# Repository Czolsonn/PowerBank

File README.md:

# STM32 Solar PowerBank

Projekt inteligentnego PowerBanka sterowanego mikrokontrolerem z rodziny **STM32F1**, integrującego ładowanie fotowoltaiczne z zaawansowanym zarządzaniem energią.

## 📋 Opis Projektu

Urządzenie łączy funkcję magazynu energii (ogniwa 18650) z inteligentnym systemem sterowania. Wykorzystuje synchroniczną przetwornicę Buck do efektywnego obniżania napięcia oraz dedykowane kontrolery USB do bezpiecznego ładowania urządzeń zewnętrznych.

### Kluczowe parametry techniczne
* **Mikrokontroler:** STM32F1xx (zarządzanie PWM, pomiary ADC, komunikacja).
* **Wejście:** Obsługa paneli fotowoltaicznych i zewnętrznych źródeł DC.
* **Wyjście:** Porty USB sterowane przez układy TPS25810 oraz TPS2514.
* **Pomiary:** Monitorowanie prądu za pomocą wzmacniacza INA180A2.

## 📂 Struktura Projektu

Repozytorium jest podzielone na sekcje sprzętową, programową oraz dokumentacyjną:

```text
.
├── 📂 Dokumentacja_peryferiów  # Noty katalogowe i opisy układów (TPS, INA, LM)
├── 📂 Obudowa_Schemat          # Pliki projektowe obudowy i poglądowe schematy
├── 📂 PowerBank_KICAD          # Projekt PCB w programie KiCad
│   ├── 📂 production           # Pliki produkcyjne (Gerber, BOM, OZE_PowerBank)
│   └── 📂 backups              # Kopie zapasowe projektu elektroniki
└── 📂 STM_C                    # Warstwa oprogramowania (Firmware)
    └── 📂 PowerBank            # Główny projekt STM32CubeIDE
        ├── 📂 Core             # Kod źródłowy aplikacji (Inc, Src, Startup)
        ├── 📂 Drivers          # Biblioteki HAL i CMSIS
        └── 📂 Debug            # Pliki binarne i logi kompilacji

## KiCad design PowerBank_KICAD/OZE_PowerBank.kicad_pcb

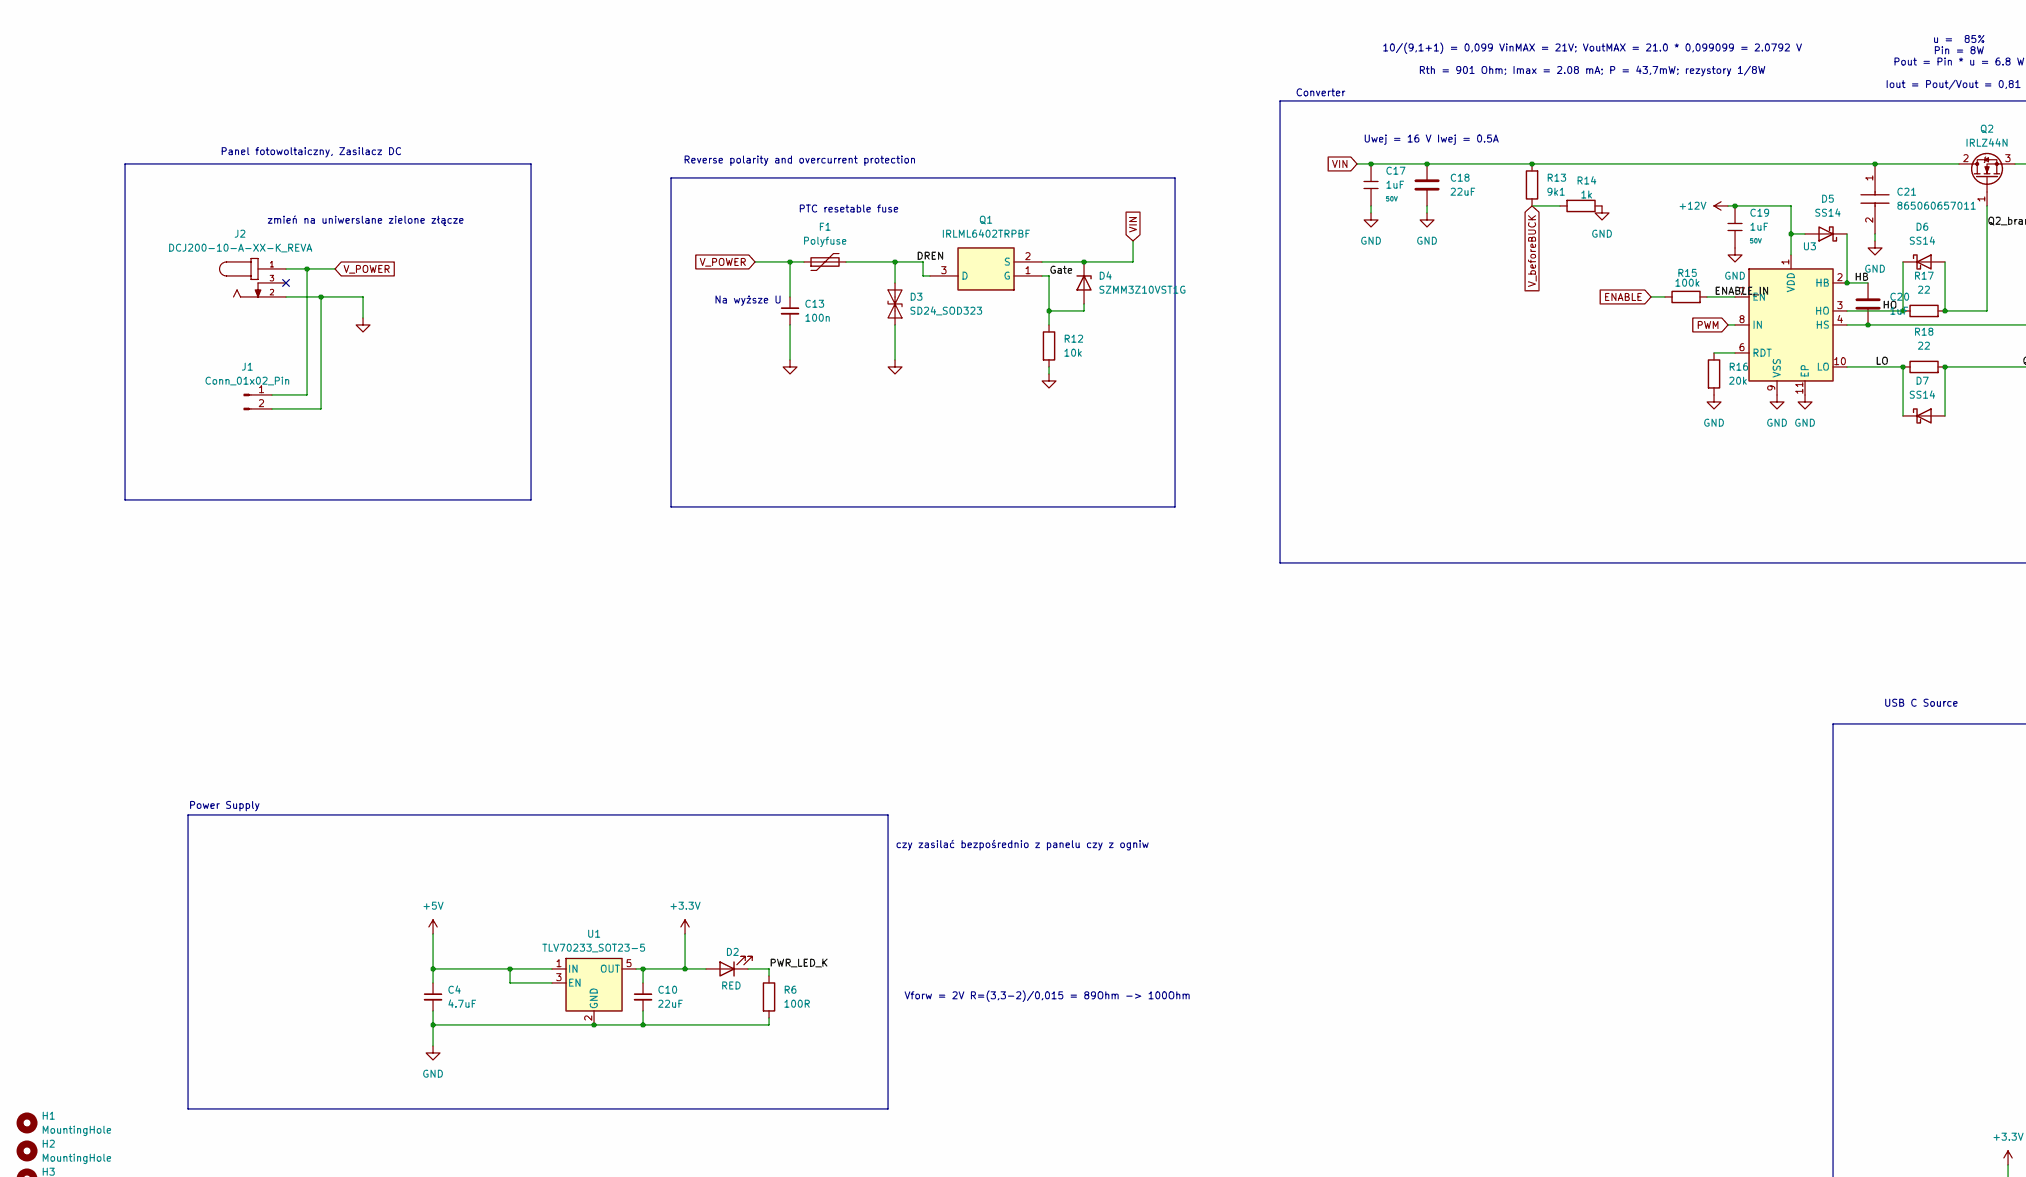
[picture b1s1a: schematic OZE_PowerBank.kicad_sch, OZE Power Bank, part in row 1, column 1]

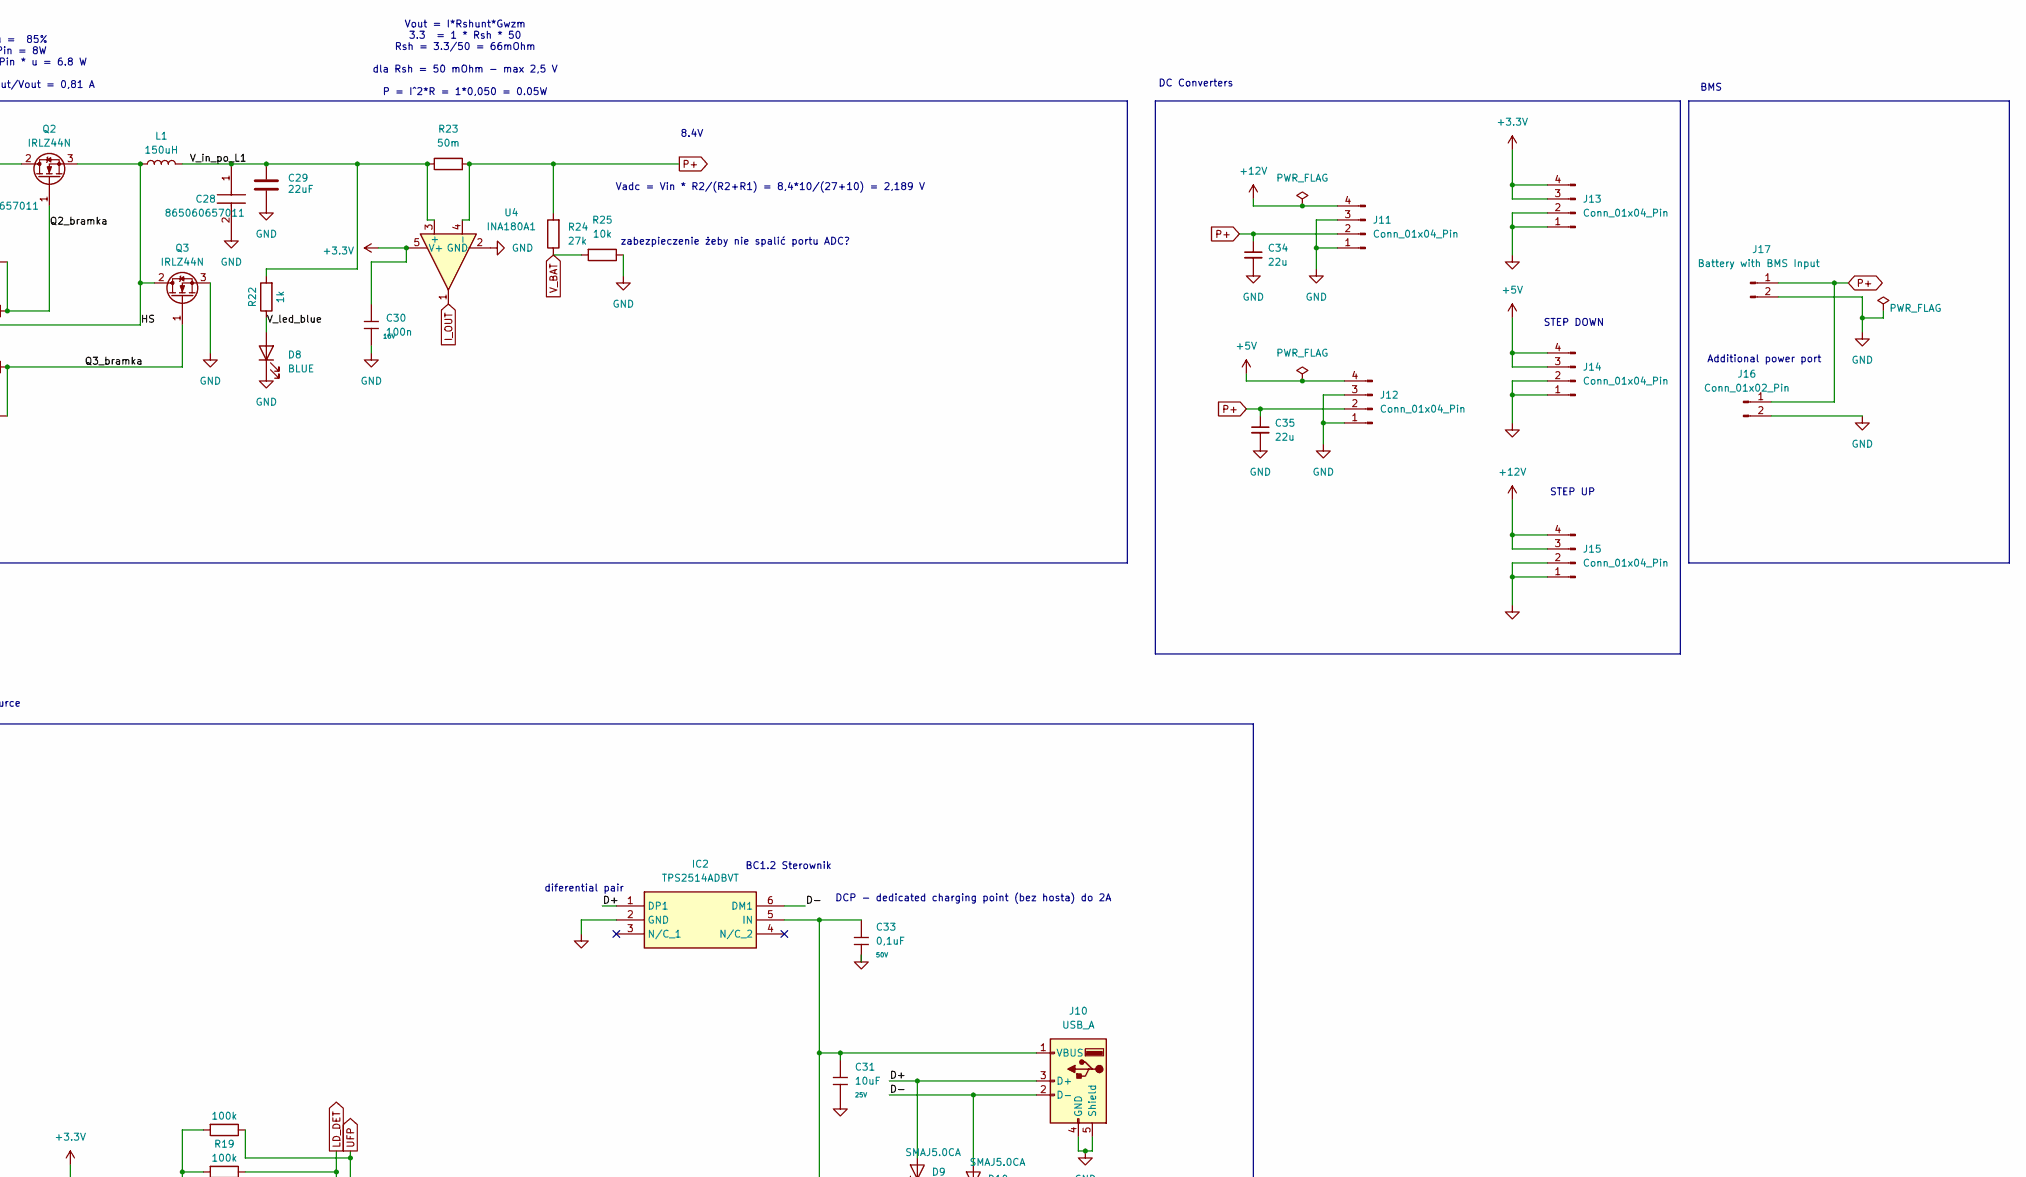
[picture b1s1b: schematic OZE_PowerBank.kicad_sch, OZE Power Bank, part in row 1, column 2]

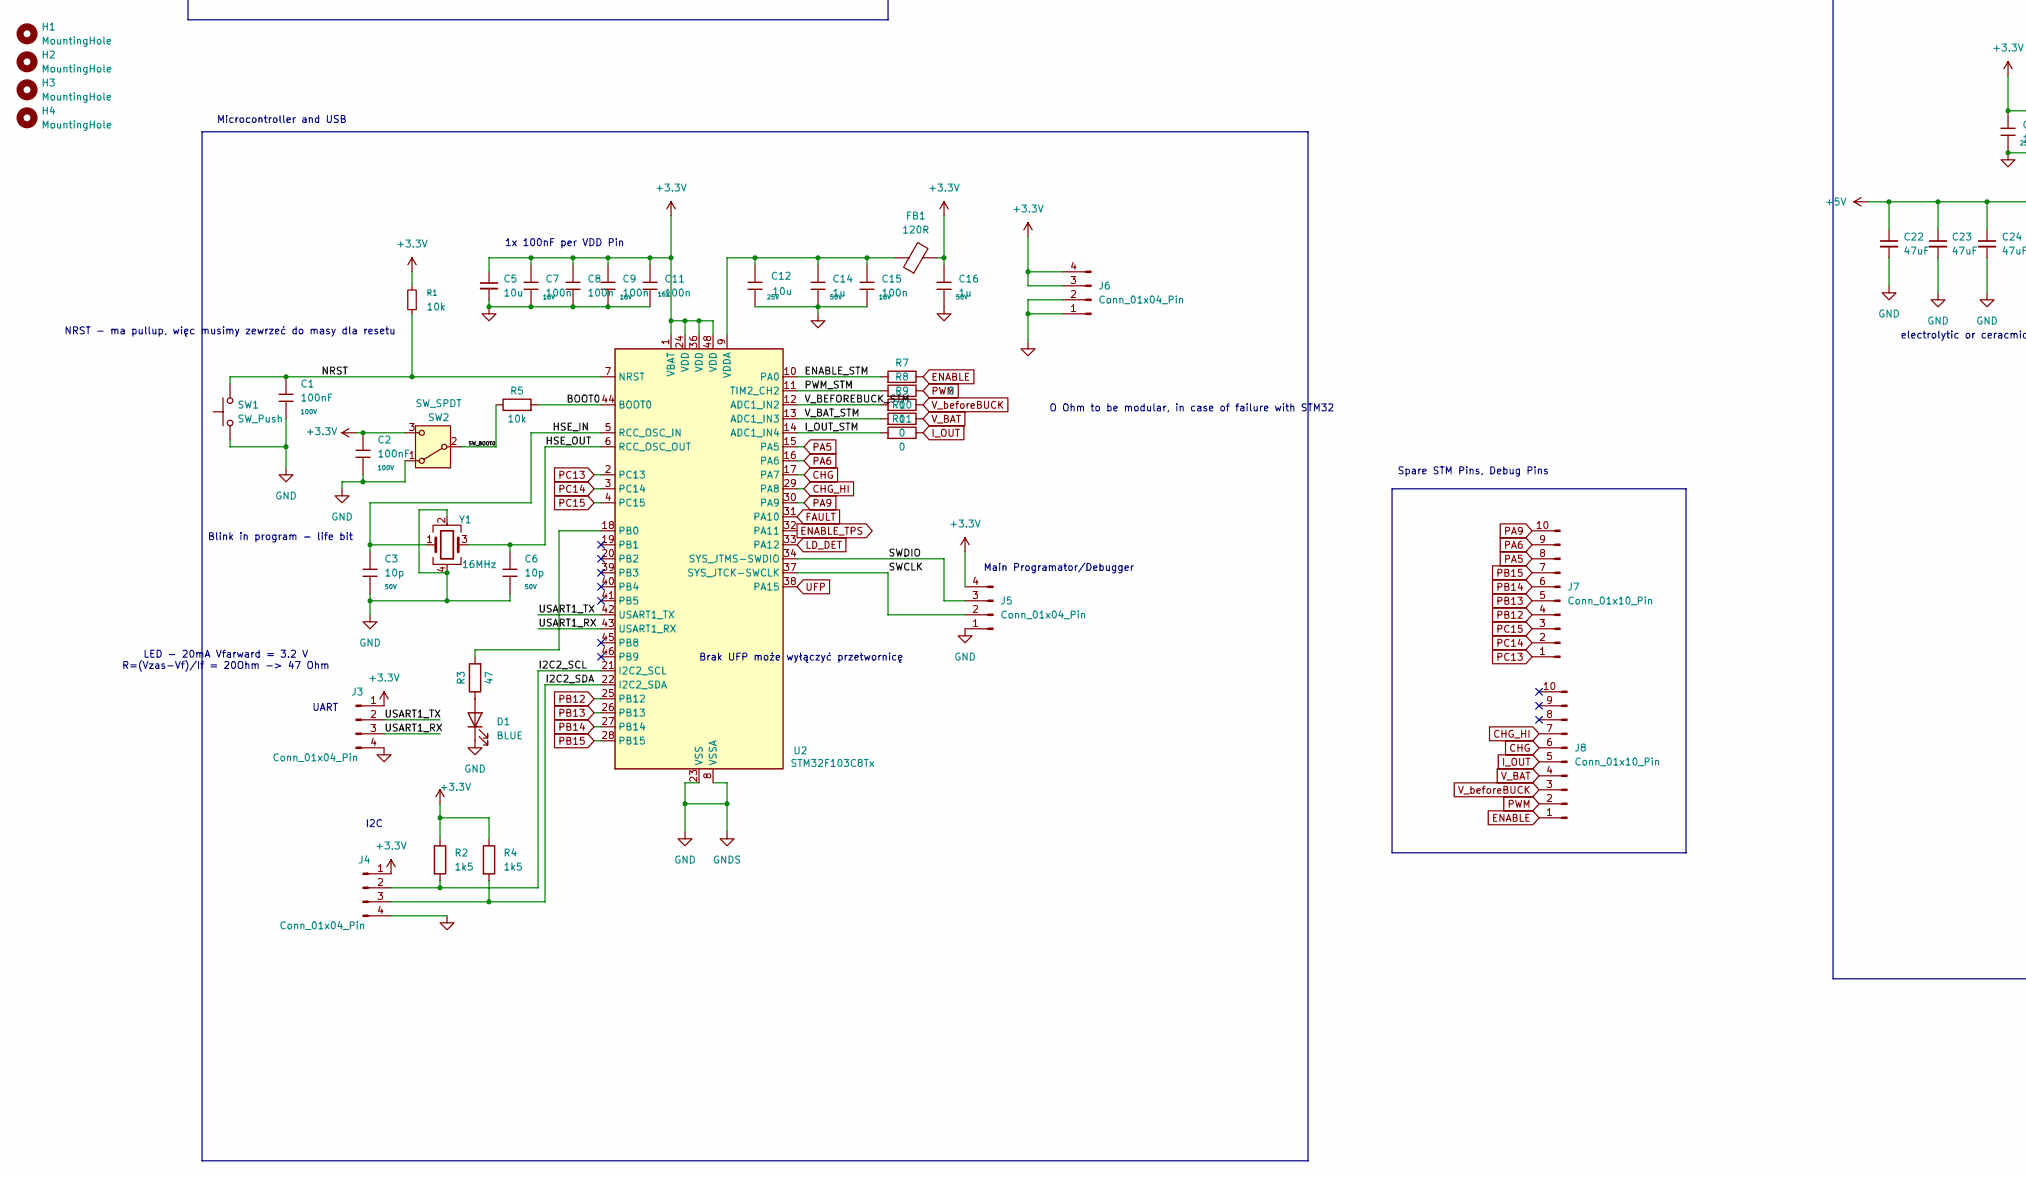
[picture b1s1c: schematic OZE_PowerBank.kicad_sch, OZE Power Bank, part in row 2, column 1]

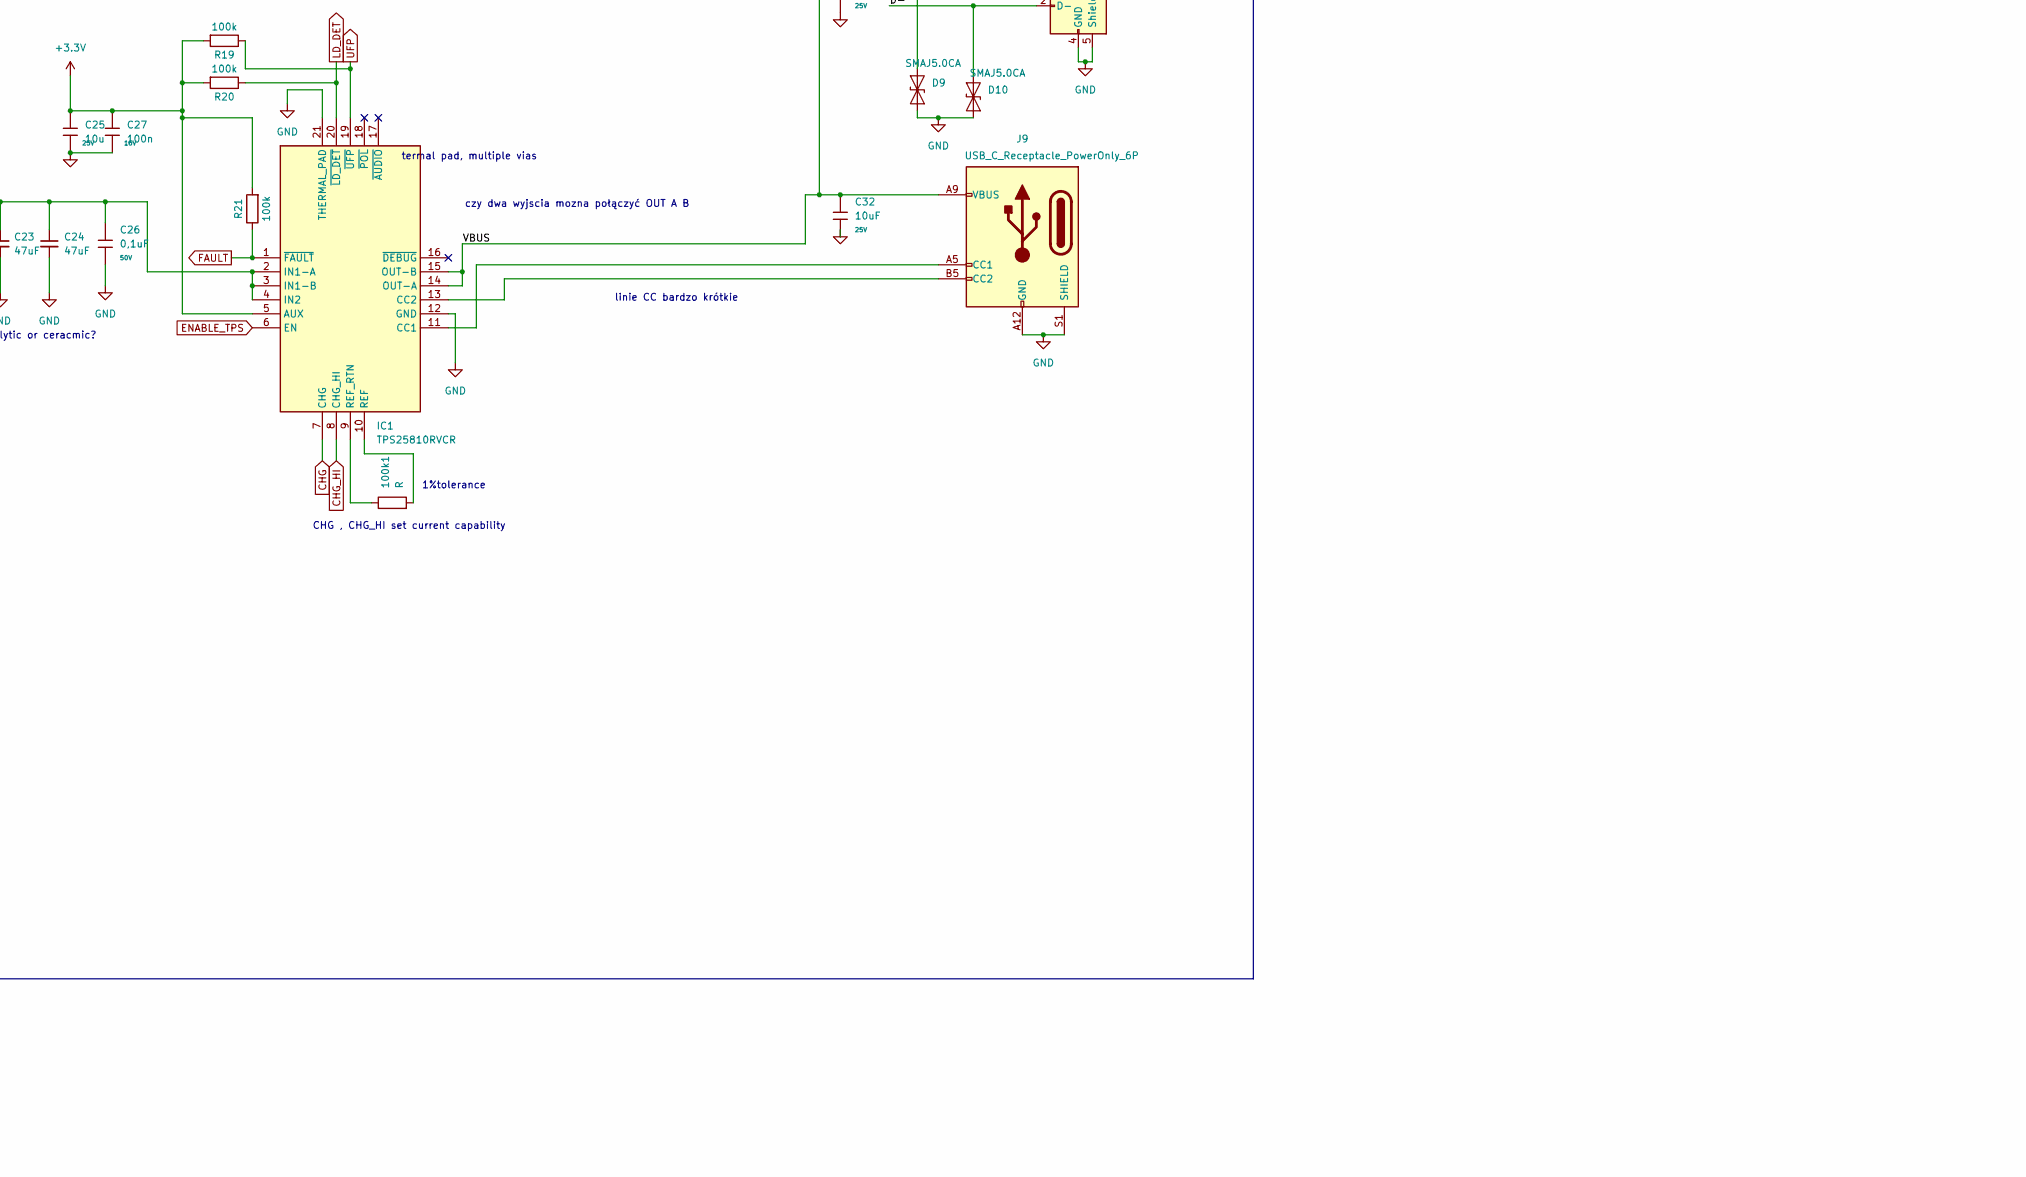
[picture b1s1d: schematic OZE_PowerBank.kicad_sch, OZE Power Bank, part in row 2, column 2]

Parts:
100k1: R; R_0603_1608Metric_Pad0.98x0.95mm_HandSolder
C1, C2: 100nF; C_0805; Voltage Rated 100V; Tolerance ±10%; Part CL21B104KCFNNNE; LCSC C28233
C3, C6: 10p; C_0402; Voltage Rated 50V; Tolerance ±5%; Part CL05C100JB5NNNC; LCSC C32949
C4: 4.7uF; C_0805_2012Metric_Pad1.18x1.45mm_HandSolder
C5: 10u; C_0805_2012Metric_Pad1.18x1.45mm_HandSolder
C7, C8, C9, C11, C15, C27, C30: 100n; C_0402; Voltage Rated 16V; Tolerance ±10%; Part CL05B104KO5NNNC; LCSC C1525
C10, C18, C29: 22uF; C_0805_2012Metric_Pad1.18x1.45mm_HandSolder
C12, C25: 10u; C_0805; Voltage Rated 25V; Tolerance ±10%; Part CL21A106KAYNNNE; LCSC C15850
C13: 100n; C_0805_2012Metric
C14, C16: 1u; C_0805; Voltage Rated 50V; Tolerance ±10%; Part CL21B105KBFNNNE; LCSC C28323
C17, C19: 1uF; C_0805; Voltage Rated 50V; Tolerance ±10%; Part CL21B105KBFNNNE; LCSC C28323
C20: 1uF; C_0805_2012Metric_Pad1.18x1.45mm_HandSolder
C21, C28: 865060657011; CAPAE1030X1050N; Mouser Part Number 710-865060657011
C22, C23, C24: 47uF; C_0805_2012Metric_Pad1.18x1.45mm_HandSolder
C26, C33: 0,1uF; C_0805; Voltage Rated 50V; Tolerance ±10%; Part CL21B105KBFNNNE; LCSC C28323
C31, C32: 10uF; C_0805; Voltage Rated 25V; Tolerance ±10%; Part CL21A106KAYNNNE; LCSC C15850
C34, C35: 22u; C_0805_2012Metric_Pad1.18x1.45mm_HandSolder
D1, D8: BLUE; LED_1206_3216Metric_Pad1.42x1.75mm_HandSolder
D2: RED; LED_1206_3216Metric_Pad1.42x1.75mm_HandSolder
D3: SD24_SOD323; D_SOD-323
D4: SZMM3Z10VST1G; D_SOD-323
D5, D6, D7: SS14; D_SMA
D9, D10: SMAJ5.0CA; D_SMA
F1: Polyfuse; Fuse_2920_7451Metric_Pad2.10x5.45mm_HandSolder
FB1: 120R; R_0603_1608Metric_Pad0.98x0.95mm_HandSolder
H1, H2, H3, H4: MountingHole; MountingHole_2.2mm_M2_ISO7380
IC1: TPS25810RVCR; QFN50P300X400X80-21N; Mouser Part Number 595-TPS25810RVCR
IC2: TPS2514ADBVT; SOT95P280X145-6N; Mouser Part Number 595-TPS2514ADBVT
J1: Conn_01x02_Pin; TerminalBlock_Phoenix_PT-1,5-2-5.0-H_1x02_P5.00mm_Horizontal
J2: DCJ200-10-A-XX-K_REVA; BarrelJack_GCT_DCJ200-10-A_Horizontal; PARTREV A
J3, J4, J5, J6, J13, J14, J15: Conn_01x04_Pin; PinSocket_1x04_P2.54mm_Vertical
J7, J8: Conn_01x10_Pin; PinSocket_1x10_P2.54mm_Vertical
J9: USB_C_Receptacle_PowerOnly_6P; USB_C_Receptacle_GCT_USB4125-xx-x-0190_6P_TopMnt_Horizontal
J10: USB_A; USB_A_TE_292303-7_Horizontal
J11: Conn_01x04_Pin; TerminalBlock_Phoenix_PT-1,5-4-3.5-H_1x04_P3.50mm_Horizontal
J12: Conn_01x04_Pin; TerminalBlock_Phoenix_PT-1,5-4-5.0-H_1x04_P5.00mm_Horizontal
J16: Conn_01x02_Pin; JST_XH_B2B-XH-A_1x02_P2.50mm_Vertical
J17: Battery with BMS Input; TerminalBlock_Phoenix_PT-1,5-2-5.0-H_1x02_P5.00mm_Horizontal
L1: 150uH; L_Pulse_PA4320
Q1: IRLML6402TRPBF; SOT95P237X112-3N; Mouser Part Number 942-IRLML6402TRPBF
Q2, Q3: IRLZ44N; TO-220-3_Vertical
R1, R5, R12, R25: 10k; R_0805_2012Metric_Pad1.20x1.40mm_HandSolder
R2, R4: 1k5; R_0805_2012Metric_Pad1.20x1.40mm_HandSolder
R3: 47; R_0805_2012Metric_Pad1.20x1.40mm_HandSolder
R6: 100R; R_0805_2012Metric_Pad1.20x1.40mm_HandSolder
R7, R8, R9, R10, R11: 0; R_0805; Overload Voltage (Max) 150V; Tolerance ±1%; Part 0805W8F0000T5E; LCSC C17477
R13: 9k1; R_0805_2012Metric_Pad1.20x1.40mm_HandSolder
R14, R22: 1k; R_0805_2012Metric_Pad1.20x1.40mm_HandSolder
R15, R19, R20, R21: 100k; R_0402_1005Metric
R16: 20k; R_0805_2012Metric_Pad1.20x1.40mm_HandSolder
R17, R18: 22; R_0805_2012Metric_Pad1.20x1.40mm_HandSolder
R23: 50m; R_1206_3216Metric_Pad1.30x1.75mm_HandSolder
R24: 27k; R_0805_2012Metric_Pad1.20x1.40mm_HandSolder
SW1: SW_Push; SW_PUSH-12mm_Wuerth-430476085716
SW2: SW_SPDT; SLW12768644AD
U1: TLV70233_SOT23-5; SOT-23-5
U2: STM32F103C8Tx; LQFP-48_7x7mm_P0.5mm
U3: LM5106SD; WSON-10-1EP_4x4mm_P0.8mm_EP2.6x3mm_ThermalVias
U4: INA180A1; SOT-23-5
Y1: 16MHz; LFXTAL071744Reel

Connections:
+3.3V: C2.1, C5.1, C7.1, C8.1, C9.1, C10.1, C11.1, C16.1, C25.1, C27.1, C30.1, D2.2 (A), FB1.2, IC1.5 (AUX), J3.1, J4.1, J5.4, J6.3, J6.4, J13.3, J13.4, R1.2, R2.1, R4.1, R19.2, R20.2, R21.2, SW2.3 (C), U1.5 (OUT), U2.1 (VBAT), U2.24 (VDD), U2.36 (VDD), U2.48 (VDD), U4.5 (V+)
+5V: C4.1, C22.1, C23.1, C24.1, C26.1, IC1.2 (IN1-A), IC1.3 (IN1-B), IC1.4 (IN2), J12.4, J14.3, J14.4, U1.1 (IN), U1.3 (EN)
+12V: C19.1, D5.2 (A), J11.4, J15.3, J15.4, U3.1 (VDD)
/BOOT0: R5.2, U2.44 (BOOT0)
/D+: D9.1 (A1), IC2.1 (DP1), J10.3 (D+)
/D-: D10.1 (A1), IC2.6 (DM1), J10.2 (D-)
/DREN: D3.2 (A2), F1.2, Q1.3 (D)
/ENABLE_IN: R15.2, U3.7 (EN)
/ENABLE_STM: R7.1, U2.10 (PA0)
/Gate: D4.2 (A), Q1.1 (G), R12.1
/HB: C20.1, D5.1 (K), U3.2 (HB)
/HO: D6.1 (K), R17.1, U3.3 (HO)
/HS: C20.2, L1.1, Q2.3 (S), Q3.2 (D), U3.4 (HS)
/HSE_IN: C3.1, U2.5 (RCC_OSC_IN), Y1.1
/HSE_OUT: C6.1, U2.6 (RCC_OSC_OUT), Y1.3
/I2C2_SCL: J4.2, R2.2, U2.21 (I2C2_SCL)
/I2C2_SDA: J4.3, R4.2, U2.22 (I2C2_SDA)
/I_OUT_STM: R11.1, U2.14 (ADC1_IN4)
/LO: D7.1 (K), R18.1, U3.10 (LO)
/NRST: C1.1, R1.1, SW1.2, U2.7 (NRST)
/PWM_STM: R8.1, U2.11 (TIM2_CH2)
/PWR_LED_K: D2.1 (K), R6.1
/Q2_bramka: D6.2 (A), Q2.1 (G), R17.2
/Q3_bramka: D7.2 (A), Q3.1 (G), R18.2
/SWCLK: J5.2, U2.37 (SYS_JTCK-SWCLK)
/SWDIO: J5.3, U2.34 (SYS_JTMS-SWDIO)
/SW_BOOT0: R5.1, SW2.2 (B)
/USART1_RX: J3.3, U2.43 (USART1_RX)
/USART1_TX: J3.2, U2.42 (USART1_TX)
/VBUS: C31.2, C32.1, C33.1, IC1.14 (OUT-A), IC1.15 (OUT-B), IC2.5 (IN), J9.A9 (VBUS), J9.B9 (VBUS), J10.1 (VBUS)
/V_BAT_STM: R10.1, U2.13 (ADC1_IN3)
/V_BEFOREBUCK_STM: R9.1, U2.12 (ADC1_IN2)
/V_in_po_L1: C28.1 (+), C29.1, L1.2, R22.2, R23.1, U4.3 (+)
/V_led_blue: D8.2 (A), R22.1
CHG: IC1.7 (CHG), J8.6, U2.17 (PA7)
CHG_HI: IC1.8 (CHG_HI), J8.7, U2.29 (PA8)
ENABLE: J8.1, R7.2, R15.1
ENABLE_TPS: IC1.6 (EN), U2.32 (PA11)
FAULT: IC1.1 (~FAULT), R21.1, U2.31 (PA10)
GND: C1.2, C2.2, C3.2, C4.2, C5.2, C6.2, C7.2, C8.2, C9.2, C10.2, C11.2, C12.2, C13.2, C14.2, C15.2, C16.2, C17.2, C18.2, C19.2, C21.2 (-), C22.2, C23.2, C24.2, C25.2, C26.2, C27.2, C28.2 (-), C29.2, C30.2, C31.1, C32.2, C33.2, C34.2, C35.2, D1.1 (K), D3.1 (A1), D8.1 (K), D9.2 (A2), D10.2 (A2), IC1.12 (GND), IC1.21 (THERMAL_PAD), IC2.2 (GND), J1.2, J2.2, J3.4, J4.4, J5.1, J6.1, J6.2, J9.A12 (GND), J9.B12 (GND), J9.S1 (SHIELD), J10.4 (GND), J10.5 (Shield), J11.1, J11.3, J12.1, J12.3, J13.1, J13.2, J14.1, J14.2, J15.1, J15.2, J16.2, J17.2, Q3.3 (S), R6.2, R12.2, R14.1, R16.2, R25.1, SW1.1, SW2.1 (A), U1.2 (GND), U2.8 (VSSA), U2.23 (VSS), U2.35 (VSS), U2.47 (VSS), U3.9 (VSS), U3.11 (EP), U3.12, U4.2 (GND), Y1.2, Y1.4
I_OUT: J8.5, R11.2, U4.1
LD_DET: IC1.20 (~LD_DET), R20.1, U2.33 (PA12)
unnamed: D1.2 (A), R3.1
unnamed: IC1.11 (CC1), J9.A5 (CC1)
unnamed: IC1.13 (CC2), J9.B5 (CC2)
unnamed: 100k1.2, IC1.10 (REF)
unnamed: 100k1.1, IC1.9 (REF_RTN)
unnamed: R3.2, U2.18 (PB0)
unnamed: C12.1, C14.1, C15.1, FB1.1, U2.9 (VDDA)
unnamed: R16.1, U3.6 (RDT)
P+: C34.1, C35.1, J11.2, J12.2, J16.1, J17.1, R23.2, R24.2, U4.4 (-)
PA5: J7.8, U2.15 (PA5)
PA6: J7.9, U2.16 (PA6)
PA9: J7.10, U2.30 (PA9)
PB12: J7.4, U2.25 (PB12)
PB13: J7.5, U2.26 (PB13)
PB14: J7.6, U2.27 (PB14)
PB15: J7.7, U2.28 (PB15)
PC13: J7.1, U2.2 (PC13)
PC14: J7.2, U2.3 (PC14)
PC15: J7.3, U2.4 (PC15)
PWM: J8.2, R8.2, U3.8 (IN)
UFP: IC1.19 (~UFP), R19.1, U2.38 (PA15)
VIN: C17.1, C18.1, C21.1 (+), D4.1 (K), Q1.2 (S), Q2.2 (D), R13.2
V_BAT: J8.4, R10.2, R24.1, R25.2
V_POWER: C13.1, F1.1, J1.1, J2.1
V_beforeBUCK: J8.3, R9.2, R13.1, R14.2

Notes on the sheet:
STEP UP
zmień na uniwerslane zielone złącze
Blink in program - life bit
u = 85% Pin = 8W Pout = Pin * u = 6.8 W Iout = Pout/Vout = 0,81 A
NRST - ma pullup, więc musimy zewrzeć do masy dla resetu
diferential pair
Reverse polarity and overcurrent protection
Microcontroller and USB
Uwej = 16 V Iwej = 0.5A
STEP DOWN
DCP - dedicated charging point (bez hosta) do 2A
Spare STM Pins, Debug Pins
PTC resetable fuse
linie CC bardzo krótkie
O Ohm to be modular, in case of failure with STM32
CHG , CHG_HI set current capability
BC1.2 Sterownik
1x 100nF per VDD Pin
Vadc = Vin * R2/(R2+R1) = 8,4*10/(27+10) = 2,189 V
Brak UFP może wyłączyć przetwornicę
I2C
Na wyższe U
Vforw = 2V R=(3,3-2)/0,015 = 89Ohm -> 100Ohm
czy zasilać bezpośrednio z panelu czy z ogniw
LED - 20mA Vfarward = 3.2 V R=(Vzas-Vf)/If = 20Ohm -> 47 Ohm
zabezpieczenie żeby nie spalić portu ADC?
DC Converters
Main Programator/Debugger
UART
Vout = I*Rshunt*Gwzm 3.3 = 1 * Rsh * 50 Rsh = 3.3/50 = 66mOhm dla Rsh = 50 mOhm - max 2,5 V P = I^2*R = 1*0,050 = 0.05W
USB C Source
Converter
1%tolerance
8.4V
Additional power port
Panel fotowoltaiczny, Zasilacz DC
termal pad, multiple vias
czy dwa wyjscia mozna połączyć OUT A B
BMS
Power Supply

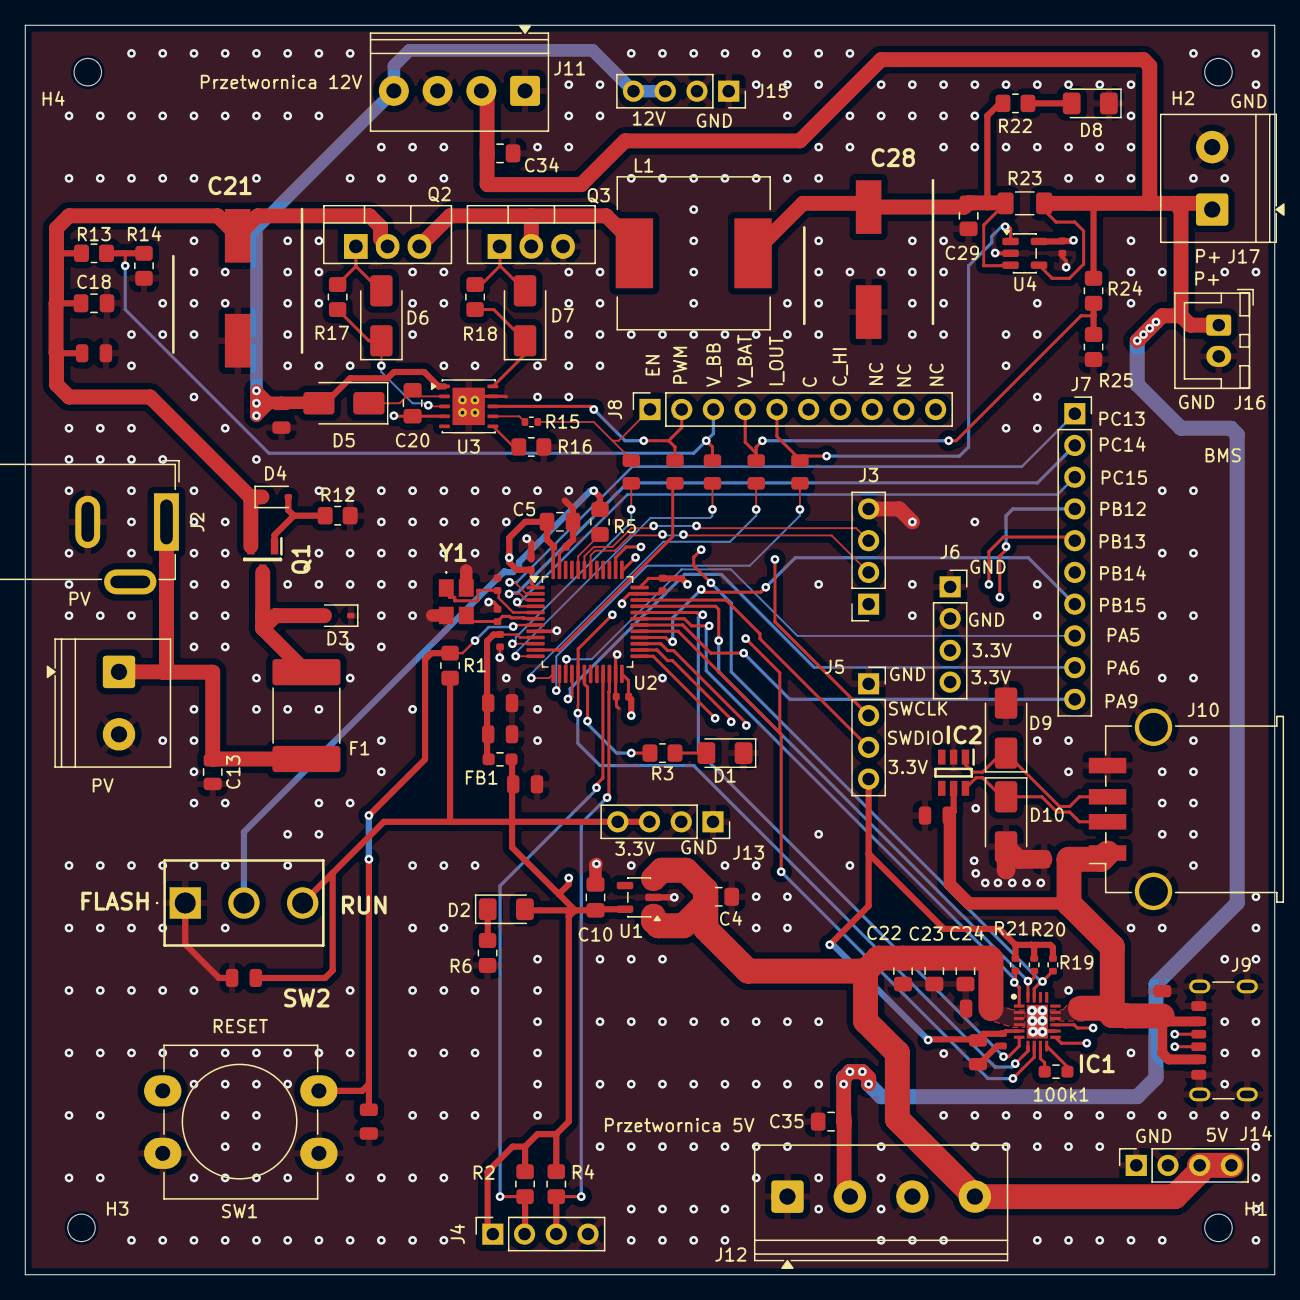
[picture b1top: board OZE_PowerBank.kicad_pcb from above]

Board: 4 copper layers, 100.0 x 100.0 mm, 107 parts (0 on the bottom side), 67 nets.

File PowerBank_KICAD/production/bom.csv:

Designator,Footprint,Quantity,Value,LCSC Part #
100K1,0603,1,R,
"C1, C2",C_0805,2,100nF,C28233
"C10, C18, C29",0805,3,22uF,
"C11, C15, C27, C30, C7, C8, C9",C_0402,7,100n,C1525
"C12, C25",C_0805,2,10u,C15850
C13,0805,1,100n,
"C14, C16",C_0805,2,1u,C28323
"C17, C19",C_0805,2,1uF,C28323
C20,0805,1,1uF,
"C21, C28",CAPAE1030X1050N,2,865060657011,
"C22, C23, C24",0805,3,47uF,
"C26, C33",C_0805,2,"0,1uF",C28323
"C3, C6",C_0402,2,10p,C32949
"C31, C32",C_0805,2,10uF,C15850
"C34, C35",0805,2,22u,
C4,0805,1,4.7uF,
C5,0805,1,10u,
"D1, D8",1206,2,BLUE,
"D10, D9",D_SMA,2,SMAJ5.0CA,
D2,1206,1,RED,
D3,D_SOD-323,1,SD24_SOD323,
D4,D_SOD-323,1,SZMM3Z10VST1G,
"D5, D6, D7",D_SMA,3,SS14,
F1,2920,1,Polyfuse,
FB1,0603,1,120R,
IC1,QFN50P300X400X80-21N,1,TPS25810RVCR,
IC2,SOT95P280X145-6N,1,TPS2514ADBVT,
J1,"TerminalBlock_Phoenix_PT-1,5-2-5.0-H_1x02_P5.00mm_Horizontal",1,Conn_01x02_Pin,
J10,USB_A_TE_292303-7_Horizontal,1,USB_A,
J11,"TerminalBlock_Phoenix_PT-1,5-4-3.5-H_1x04_P3.50mm_Horizontal",1,Conn_01x04_Pin,
J12,"TerminalBlock_Phoenix_PT-1,5-4-5.0-H_1x04_P5.00mm_Horizontal",1,Conn_01x04_Pin,
"J13, J14, J15, J3, J4, J5, J6",PinSocket_1x04_P2.54mm_Vertical,7,Conn_01x04_Pin,
J16,JST_XH_B2B-XH-A_1x02_P2.50mm_Vertical,1,Conn_01x02_Pin,
J17,"TerminalBlock_Phoenix_PT-1,5-2-5.0-H_1x02_P5.00mm_Horizontal",1,Battery with BMS Input,
J2,BarrelJack_GCT_DCJ200-10-A_Horizontal,1,DCJ200-10-A-XX-K_REVA,
"J7, J8",PinSocket_1x10_P2.54mm_Vertical,2,Conn_01x10_Pin,
J9,USB_C_Receptacle_GCT_USB4125-xx-x-0190_6P_TopMnt_Horizontal,1,USB_C_Receptacle_PowerOnly_6P,
L1,L_Pulse_PA4320,1,150uH,
Q1,SOT95P237X112-3N,1,IRLML6402TRPBF,
"Q2, Q3",TO-220-3_Vertical,2,IRLZ44N,
"R1, R12, R25, R5",0805,4,10k,
"R10, R11, R7, R8, R9",R_0805,5,0,C17477
R13,0805,1,9k1,
"R14, R22",0805,2,1k,
"R15, R19, R20, R21",0402,4,100k,
R16,0805,1,20k,
"R17, R18",0805,2,22,
"R2, R4",0805,2,1k5,
R23,1206,1,50m,
R24,0805,1,27k,
R3,0805,1,47,
R6,0805,1,100R,
SW1,SW_PUSH-12mm_Wuerth-430476085716,1,SW_Push,
SW2,SLW12768644AD,1,SW_SPDT,
U1,SOT-23-5,1,TLV70233_SOT23-5,
U2,LQFP-48_7x7mm_P0.5mm,1,STM32F103C8Tx,
U3,WSON-10-1EP_4x4mm_P0.8mm_EP2.6x3mm_ThermalVias,1,LM5106SD,
U4,SOT-23-5,1,INA180A1,
Y1,LFXTAL071744Reel,1,16MHz,

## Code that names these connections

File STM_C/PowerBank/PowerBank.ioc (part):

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Mcu.Name=STM32F103C(8-B)Tx
Mcu.Package=LQFP48
Mcu.UserName=STM32F103C8Tx
PA0-WKUP.GPIOParameters=GPIO_Label
PA0-WKUP.GPIO_Label=ENABLE
PA0-WKUP.Signal=GPIO_Output
PA1.GPIOParameters=GPIO_Label
PA1.GPIO_Label=PWM
PA1.Signal=S_TIM2_CH2
PA10.GPIOParameters=GPIO_PuPd,GPIO_Label,GPIO_ModeDefaultEXTI
PA10.GPIO_Label=FAULT
PA10.GPIO_ModeDefaultEXTI=GPIO_MODE_IT_FALLING
PA10.GPIO_PuPd=GPIO_PULLUP
PA10.Signal=GPXTI10
PA11.GPIOParameters=GPIO_Label
PA11.GPIO_Label=ENABLE_TPS
PA11.Signal=GPIO_Output
PA12.GPIOParameters=GPIO_PuPd,GPIO_Label
PA12.GPIO_Label=LD_DET
PA12.GPIO_PuPd=GPIO_PULLDOWN
PA12.Signal=GPIO_Input
PA13.Mode=Serial_Wire
PA13.Signal=SYS_JTMS-SWDIO
PA14.Mode=Serial_Wire
PA14.Signal=SYS_JTCK-SWCLK
PA15.GPIOParameters=GPIO_PuPd,GPIO_Label
PA15.GPIO_Label=UFP
PA15.GPIO_PuPd=GPIO_PULLDOWN
PA15.Signal=GPIO_Input
PA2.GPIOParameters=GPIO_Label,GPIO_Mode
PA2.GPIO_Label=V_BB
PA2.GPIO_Mode=GPIO_MODE_ANALOG
PA2.Signal=ADCx_IN2
PA3.GPIOParameters=GPIO_Label,GPIO_Mode
PA3.GPIO_Label=V_BAT
PA3.GPIO_Mode=GPIO_MODE_ANALOG
PA3.Signal=ADCx_IN3
PA4.GPIOParameters=GPIO_Label,GPIO_Mode
PA4.GPIO_Label=I_OUT
PA4.GPIO_Mode=GPIO_MODE_ANALOG
PA4.Signal=ADCx_IN4
PA7.GPIOParameters=GPIO_PuPd,GPIO_Label
PA7.GPIO_Label=CHG
PA7.GPIO_PuPd=GPIO_PULLDOWN
PA7.Signal=GPIO_Input
PA8.GPIOParameters=GPIO_PuPd,GPIO_Label
PA8.GPIO_Label=CHG_HI
PA8.GPIO_PuPd=GPIO_PULLDOWN
PA8.Signal=GPIO_Input
PB0.GPIOParameters=GPIO_Label
PB0.GPIO_Label=BLUE_D
PB0.Signal=GPIO_Output
PB6.Mode=Asynchronous
PB6.Signal=USART1_TX
PB7.Mode=Asynchronous
PB7.Signal=USART1_RX
RCC.HSEDivPLL=RCC_HSE_PREDIV_DIV2
RCC.HSE_VALUE=16000000
RCC.SYSCLKFreq_VALUE=64000000
RCC.SYSCLKSource=RCC_SYSCLKSOURCE_PLLCLK
board=custom

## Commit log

2025-10-29 start
    start
2025-11-03 merging files
2025-11-03 git ignore
2025-11-03 merging gitignore
2025-11-03 oze deleted
2025-11-03 resoling issues
2025-11-03 STM project added
2025-11-03 zabezpieczenia USB C
2025-11-04 04.11
    - 150uF kondensatory to elektrolity ważny LOW RMS!
    - Przetwornica do sterownika (IMZ Przetwornica MT3608 2A Step-Up DC/DC) gotowa płytka
    - 100 kHz sterowanie PWM (tak dobrany jest dławik i kondensatory co widać na symulacji)
    Symulacja w LT Spice
2025-11-04 BMS - 04.11 21:00 Hubert
    Dodany BMS wraz z tranzystorem odcinającym masę dla układu ładowania
2025-11-05 Update 05.11 19:00 - Hubert
    Zmiany:
    - oznaczenia zasilania na schemacie
    - dodano przetwornice buck down
    - dodano masę sygnałową ???
    - po przemieszanie elementów na schemacie (czytelniej)
    - zmiana kondensatorów odpowiednich na elektrolity (polarized)
2025-11-10 zmieniony symbol biblioteczny TPS, dodano footprinty, zmieniono piny wyprowadzeniowe, dodano opis funkci pinów STM , konfiguracja kanalow ADC
2025-11-10 added footprints, i have libraries localy, give comments about calculations of elements
2025-11-12 Zmiany na schemacie
    Zmiana wzmacniacza z INA180A2 na INA180A1 bo za duże napięcie wychodziło na wyjściu i wywaliłem symulacje bo bez niej nie moge dac commita
2025-11-13 added conectors footprints
2025-11-15 PCB layout
2025-11-15 before branching
2025-11-26 26.11 Hubert - PCB
    Poprowadzone ścieżki sygnałowe, prądowe, poza 2 wchodzącymi do sterownika USB-C, USB-A . Brak wylanej masy
2025-11-27 Płytka PCB i ścieżki w zasadzie skończone 'prawie'
    Wylane warstwy, wszystkie połączenia poza dwoma od przycisku z których nie korzystamy, jeszcze są błędy jakieś związane z termal padami, ale juz możesz wprowadzać zmiany
2025-11-28 changed footprint, correct GND conection to thermal, remove some vias, give additional vias in TPS25810
2026-01-28 Kod
    Całość konfiguracji STM32CubeMX i kod programu STM32CubeIDE
2026-02-17 Porządki
    Uporządkowanie plików i nazw dodanie dokumentacji technicznej sprzętu i poprawny .gitignore
2026-02-17 Dodanie poprawnego .gitignore
2026-02-17 Porządki związane z .gitignore
2026-02-19 Dokumentacje
2026-02-19 Initialize README with project details
    Added detailed project description and structure.
